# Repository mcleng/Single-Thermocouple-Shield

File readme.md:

Single Thermocouple Shield
==========================

This work is licensed under a <a rel="license" href="http://creativecommons.org/licenses/by-sa/3.0/">Creative Commons Attribution-ShareAlike 3.0 Unported License</a>.

Designed By:

*	Ryan McLaughlin <ryan@ryanjmclaughlin.com>

Summary
-------

The thermocouple shield was based upon the original breakout board developed for the MAX6675.  While this is a great little chip it is a small surface mount part and therefore difficult to solder. The thermocouple shield helps with having the MAX31855 chip broken out to a simple 0.1" header, a direct interface the the shield, and also provides a PCB Thermocouple Connector to easily interface to a thermocouple. Thermocouple wires are not designed to be soldered and this provides a good solid connection, while also using the proper metals in the connector required for a thermocouple connection.

Connections to Arduino pins are through solder jumpers (normally-closed), however trace is easily cuttable to be able to re-map connections to different pins.  The TXB0104 level shifter to translates 5V Arduino signals to the MAX31855 (3.3V) so the shield can be used with 5V and 3.3V Arduino platforms. Arduino reset switch on the shield.  A secondary set of headers to breakout Arduino pins along sides of the shield to allow for easy prototyping or re-mapping of connections.

Tutorial
--------

It is simple to get everything up and running.

1.	Install a set of shield headers or shield stacking headers to the board
2.	(Optional) Cut solder jumpers if you need to connect the MAX31855 to different pins but adding jumpers between center header and shield pins.
3.	Connect a K-Type [Thermocouple](http://en.wikipedia.org/wiki/Thermocouple Thermocouple)
4.	Load one of the samples from the [[MAX31855 Arduino Library]] and you should see temperature information in the serial console.

Board Specs
-----------

*	Dimensions: Arduino Shield
*	Chip: MAX31855, TXB0104
*	Voltage: 5V, 3.3V
*	Header: 2 - 1x6 0.1" Pitch, 2 - 1x8 0.1" Pitch
*	Alternate Connection: 1x4 0.1" Pitch header
*	Fixturing: Matching holes to Arduino
*	Pin Connections
	*	13 - SCK
	*	12 - SO
	*	10 - CS1
	*	9 - LED1

Versions
--------

###v2.1.1
* Removed routing of status led through level shifter
* PCB Production dates: 01-2012

###v2.1

Initial release of a dedicated single channel board. The design follows the quad channel board. Other changes included:

* Initial release under Eagle 6.1 on Github
* Change to MAX31855 chip
* Reduction to a single thermocouple channel
* Addition of prototyping space on all free areas of the shield
* Change solder jumpers to be normally-closed, however trace is easily cutable
* Added TXB0104 level shifter to translate 5V Arduino signals to the MAX31855
* Added Arduino reset switch
* Added secondary set of headers to breakout Arduino pins along sides of the shield
* Updated prototyping holes to fall on same 0.1" grid as Arduino headers
* PCB Production dates: 09-2011

####Board Specs
* Dimensions: Arduino Shield
* Chip: MAX31855, TXB0104
* Voltage: 5V, 3.3V
* Header: 2 - 1x6 0.1" Pitch, 2 - 1x8 0.1" Pitch
* Fixturing: Matching holes to Arduino

Purchase
--------

[store.ryanjmclaughlin.com](http://store.ryanjmclaughlin.com). 

TODO
----

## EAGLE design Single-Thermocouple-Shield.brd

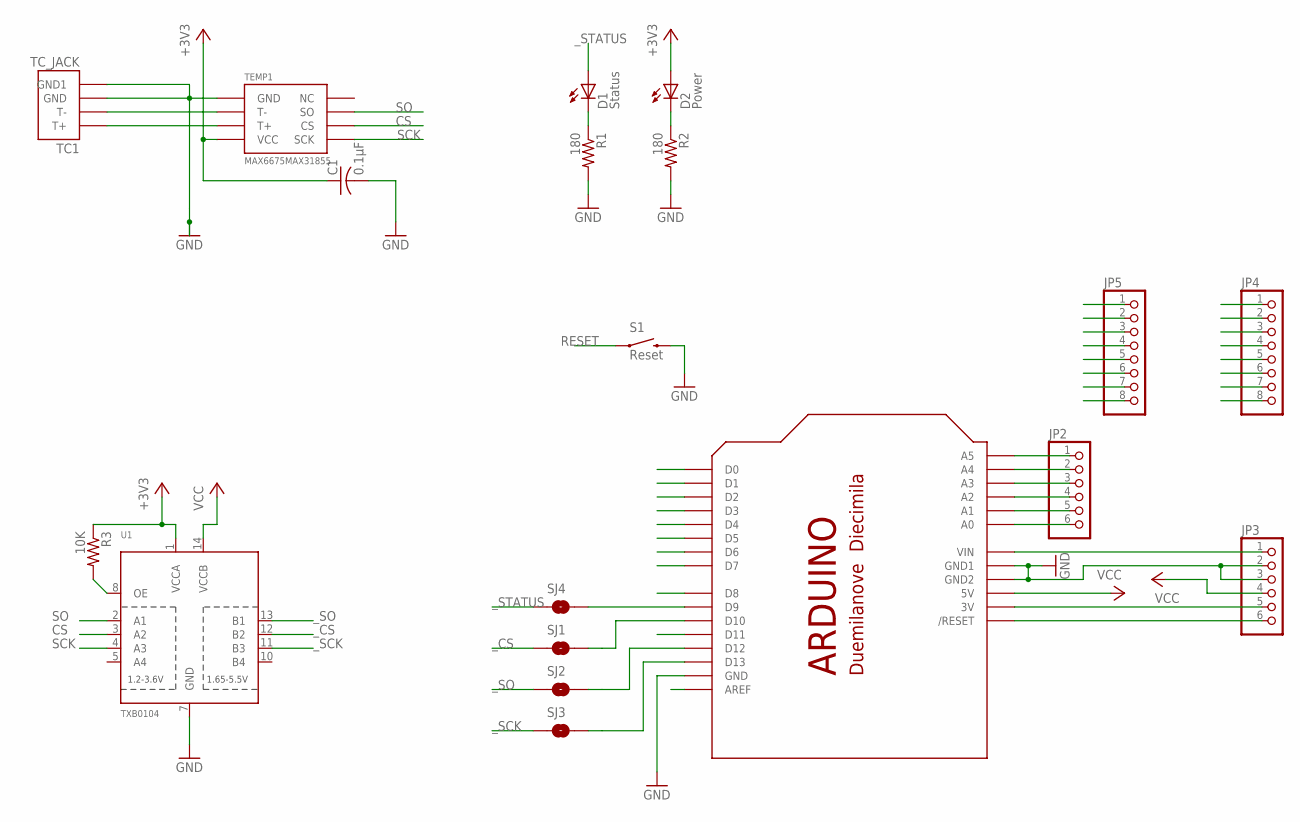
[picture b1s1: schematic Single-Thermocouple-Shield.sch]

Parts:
C1: 0.1µF; C0603
D1: Status; CHIPLED_0805
D2: Power; CHIPLED_0805
JP2, JP3: PINHD-1X6CB; 1X06-CLEANBIG
JP4, JP5: PINHD-1X8CLEANBIG; 1X08-CLEANBIG
R1, R2: 180; R0603
R3: 10K; R0603
S1: Reset; TACTILE_SWITCH_SMD
SJ1, SJ2, SJ3, SJ4: SOLDERJUMPERTRACE; SJ_2S-TRACE
TC1: TC_JACK
TEMP1: MAX6675MAX31855; SOIC-8
U1: TXB0104; TSSOP14
U$3: ARDUINOUNO; ARDUINO

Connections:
+3V3: C1.1, D2.A, JP3.5, R3.1, TEMP1.VCC, U1.1 (VCCA), U$3.3V
AREF: JP4.8, U$3.AREF
CS: TEMP1.CS, U1.3 (A2)
D0: JP5.1, U$3.D0
D1: JP5.2, U$3.D1
D2: JP5.3, U$3.D2
D3: JP5.4, U$3.D3
D4: JP5.5, U$3.D4
D5: JP5.6, U$3.D5
D6: JP5.7, U$3.D6
D7: JP5.8, U$3.D7
D8: JP4.1, U$3.D8
D9: JP4.2, SJ4.2, U$3.D9
D10: JP4.3, SJ1.2, U$3.D10
D11: JP4.4, U$3.D11
D12: JP4.5, SJ2.2, U$3.D12
D13: JP4.6, SJ3.2, U$3.D13
GND: C1.2, JP3.2, JP3.3, JP4.7, R1.2, R2.2, S1.3 (2), TC1.P$1 (GND), TC1.P$2 (GND1), TEMP1.GND, U1.7 (GND), U$3.GND, U$3.GND1, U$3.GND2
unnamed: D1.C, R1.1
unnamed: JP2.1, U$3.A5
unnamed: JP2.2, U$3.A4
unnamed: D2.C, R2.1
unnamed: JP2.3, U$3.A3
unnamed: JP2.4, U$3.A2
unnamed: R3.2, U1.8 (OE)
unnamed: JP2.5, U$3.A1
unnamed: JP2.6, U$3.A0
unnamed: JP3.1, U$3.VIN
RESET: JP3.6, S1.1, U$3.RESET (/RESET)
SCK: TEMP1.SCK, U1.4 (A3)
SO: TEMP1.SO, U1.2 (A1)
T1+: TC1.T+, TEMP1.T+
T1-: TC1.T-, TEMP1.T-
VCC: JP3.4, U1.14 (VCCB), U$3.5V
_CS: SJ1.1, U1.12 (B2)
_SCK: SJ3.1, U1.11 (B3)
_SO: SJ2.1, U1.13 (B1)
_STATUS: D1.A, SJ4.1

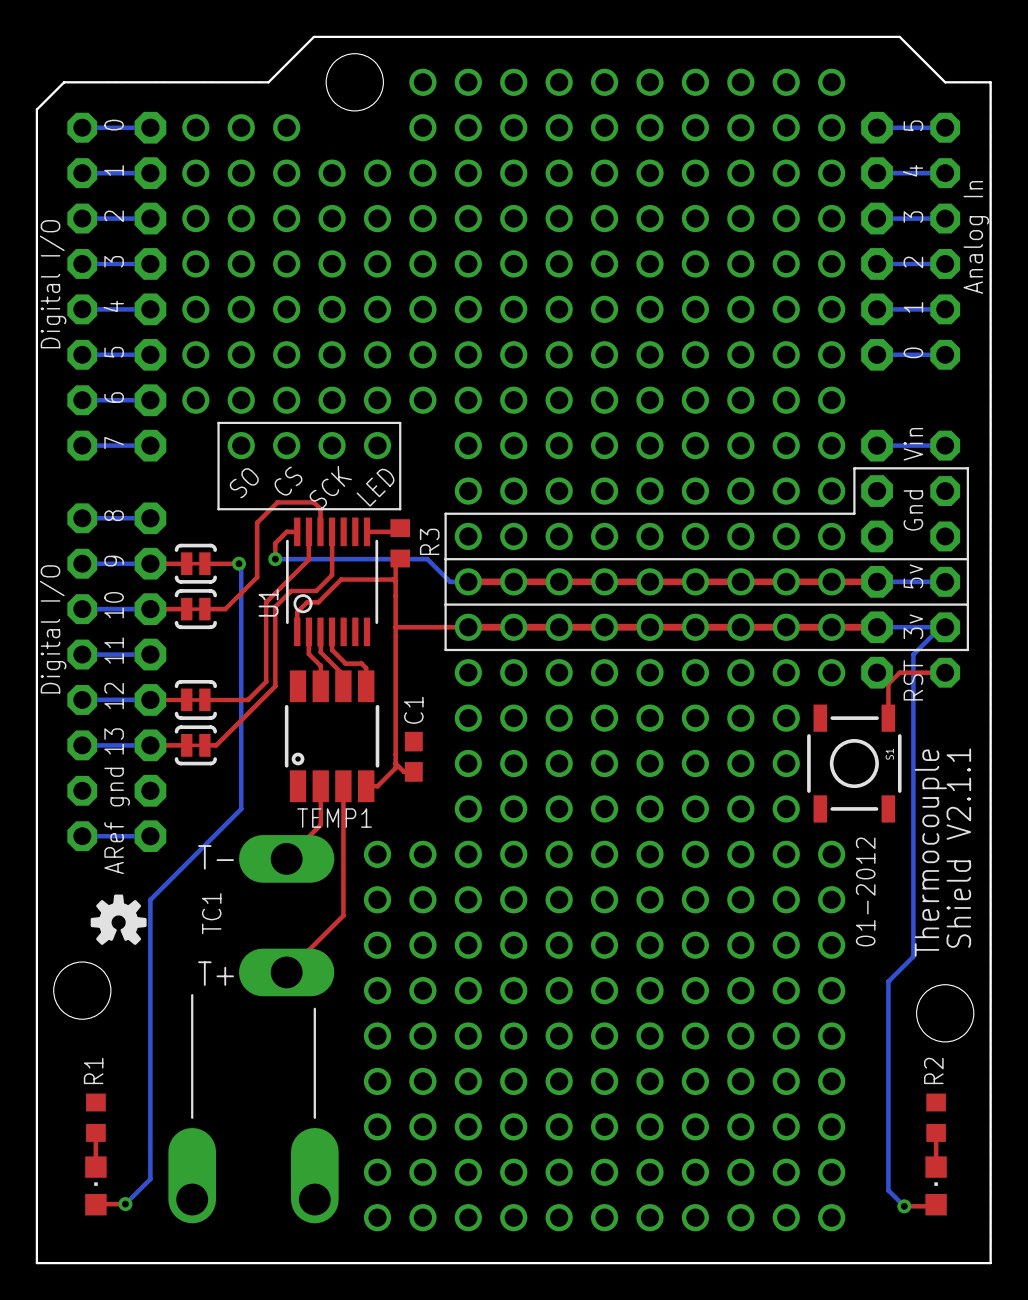
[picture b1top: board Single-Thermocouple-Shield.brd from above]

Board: 2 copper layers, 53.3 x 68.6 mm, 20 parts (0 on the bottom side), 38 nets.

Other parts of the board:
U$2: OSHW-LOGO-S

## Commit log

2012-01-29 Updated to Eagle6, board v2.1. Initial release to github
2012-01-29 Added read me file
2012-01-29 updated read me from wiki details
2012-01-29 updated for 01-2012 pcb production
2012-01-29 Removed routing of LED through level shifter
2012-01-31 Added schematic and board images/pdf

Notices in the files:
readme.md:
CC BY-SA 3.0
